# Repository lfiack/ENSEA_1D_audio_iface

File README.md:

# ENSEA_1D_audio_iface
Interface audio (carte son) pour les TP de systèmes numériques en 1D à l'ENSEA

## Make the project work
This project uses a submodule for the KiCAD library. To get it properly, use the `--recursive` option when cloning the repo :
```
git clone --recursive git@github.com:lfiack/ENSEA_1D_audio_iface.git
```

If you forgot the `--recursive` option (as I do quite often), you can type the following command :
```
git submodule update --init --recursive
```

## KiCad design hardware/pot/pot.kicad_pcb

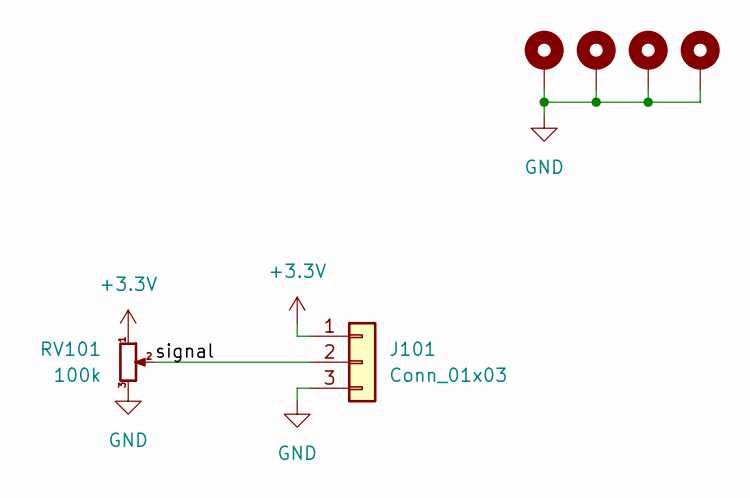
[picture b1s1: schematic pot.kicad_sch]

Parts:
H101, H102, H103, H104: MountingHole_Pad; MountingHole_3.2mm_M3_Pad
J101: Conn_01x03; JST_XH_S3B-XH-A-1_1x03_P2.50mm_Horizontal
RV101: 100k; Potentiometer_Alpha_RD901F-40-00D_Single_Vertical

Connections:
+3.3V: J101.1, RV101.1
/signal: J101.2, RV101.2
GND: H101.1, H102.1, H103.1, H104.1, J101.3, RV101.3

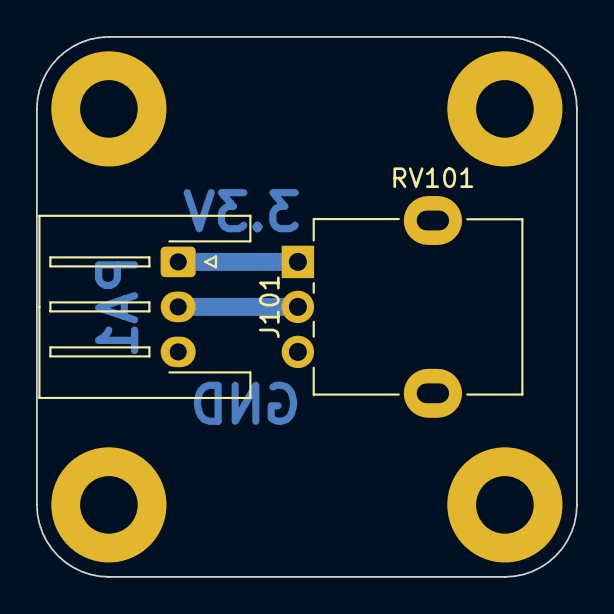
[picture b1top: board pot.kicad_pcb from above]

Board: 2 copper layers, 30.0 x 30.0 mm, 6 parts (0 on the bottom side), 3 nets.

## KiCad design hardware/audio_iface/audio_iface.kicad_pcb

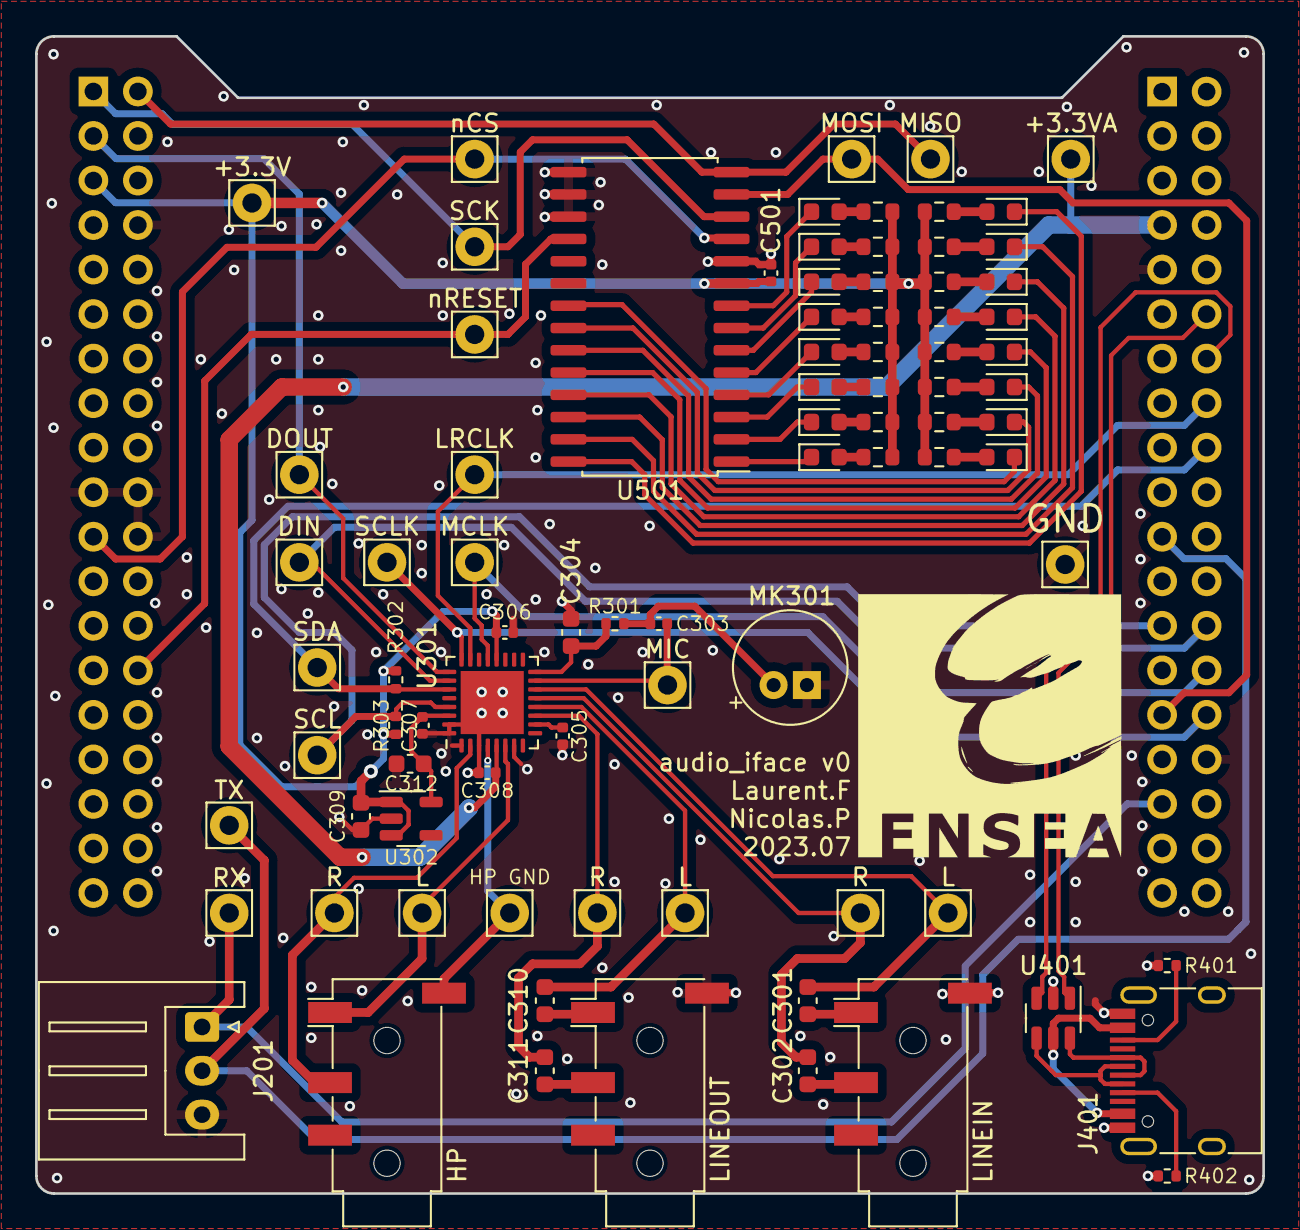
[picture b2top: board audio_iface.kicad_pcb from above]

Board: 2 copper layers, 70.0 x 66.0 mm, 86 parts (0 on the bottom side), 72 nets.

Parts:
C301, C302, C304, C310, C311: 1uF; C_0603_1608Metric
C303, C305, C306, C307, C308, C501: 100nF; C_0402_1005Metric
C309, C312: 1u; C_0603_1608Metric
D501, D502, D503, D504, D505, D509, D510, D511, D512, D513: GREEN; LED_0603_1608Metric
D506, D507, D514, D515: ORANGE; LED_0603_1608Metric
D508, D516: RED; LED_0603_1608Metric
J201: UART; JST_XH_S3B-XH-A_1x03_P2.50mm_Horizontal
J301: LINEIN; Jack_3.5mm_PJ320D_Horizontal
J302: LINEOUT; Jack_3.5mm_PJ320D_Horizontal
J303: HP; Jack_3.5mm_PJ320D_Horizontal
J401: USB_C_Receptacle_USB2.0; USB_C_Receptacle_HRO_TYPE-C-31-M-12
MK301: Microphone; Electret_ABM-713-RC
R301, R401, R402: 5.1k; R_0402_1005Metric
R302, R303: 1.5k; R_0402_1005Metric
R501, R502, R503, R504, R505, R506, R507, R508, R509, R510, R511, R512, R513, R514, R515, R516: R_Small; R_0603_1608Metric
TP101: nRESET; Pin_D1.1mm_L8.5mm_W2.5mm_FlatFork
TP102: MISO; Pin_D1.1mm_L8.5mm_W2.5mm_FlatFork
TP103: MOSI; Pin_D1.1mm_L8.5mm_W2.5mm_FlatFork
TP104: SCK; Pin_D1.1mm_L8.5mm_W2.5mm_FlatFork
TP105: nCS; Pin_D1.1mm_L8.5mm_W2.5mm_FlatFork
TP106: MCLK; Pin_D1.1mm_L8.5mm_W2.5mm_FlatFork
TP107: SCLK; Pin_D1.1mm_L8.5mm_W2.5mm_FlatFork
TP108: LRCLK; Pin_D1.1mm_L8.5mm_W2.5mm_FlatFork
TP109: DIN; Pin_D1.1mm_L8.5mm_W2.5mm_FlatFork
TP110: DOUT; Pin_D1.1mm_L8.5mm_W2.5mm_FlatFork
TP111: SCL; Pin_D1.1mm_L8.5mm_W2.5mm_FlatFork
TP112: SDA; Pin_D1.1mm_L8.5mm_W2.5mm_FlatFork
TP201: +3.3V; Pin_D1.1mm_L8.5mm_W2.5mm_FlatFork
TP202: +3.3VA; Pin_D1.1mm_L8.5mm_W2.5mm_FlatFork
TP203: RX; Pin_D1.1mm_L8.5mm_W2.5mm_FlatFork
TP204: TX; Pin_D1.1mm_L8.5mm_W2.5mm_FlatFork
TP205: GND; Pin_D1.1mm_L8.5mm_W2.5mm_FlatFork
TP301: MIC; Pin_D1.1mm_L8.5mm_W2.5mm_FlatFork
TP302, TP304, TP306: R; Pin_D1.1mm_L8.5mm_W2.5mm_FlatFork
TP303, TP305, TP308: L; Pin_D1.1mm_L8.5mm_W2.5mm_FlatFork
TP307: HP GND; Pin_D1.1mm_L8.5mm_W2.5mm_FlatFork
U201: NUCLEO_L476RG; ST_NUCLEO_64
U301: SGTL5000XNAA3; QFN-32-1EP_5x5mm_P0.5mm_EP3.6x3.6mm
U302: BU18SD2MG-MTR; SOT-23-5
U401: USBLC6-2SC6; SOT-23-6
U501: MCP23S17-E/SO; SOIC-28W_7.5x17.9mm_P1.27mm

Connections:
+1V8: C307.1, C312.1, U301.30 (VDDD), U302.5 (OUT)
+3.3V: C306.1, C309.1, C501.1, R302.1, R303.1, R501.2, R502.2, R503.2, R504.2, R505.2, R506.2, R507.2, R508.2, R509.2, R510.2, R511.2, R512.2, R513.2, R514.2, R515.2, R516.2, TP201.1, U201.105 (VDD), U301.20 (VDDIO), U302.1 (IN), U302.3 (STBY), U501.9 (VDD)
+3.3VA: C308.1, TP202.1, U201.207 (AVDD), U301.5 (VDDA)
/AUDIO CODEC/HP_L: J303.T, TP308.1, U301.6 (HP_L)
/AUDIO CODEC/HP_R: J303.R1, TP306.1, U301.2 (HP_R)
/AUDIO CODEC/HP_VGND: J303.S, TP307.1, U301.4 (HP_VGND)
/AUDIO CODEC/I2C_SCL: R303.2, TP111.1, U201.225 (PB10), U301.29 (CTRL_CLK)
/AUDIO CODEC/I2C_SDA: R302.2, TP112.1, U201.218 (PB11), U301.27 (CTRL_DATA)
/AUDIO CODEC/I2S_DIN: TP109.1, U201.226 (PB15), U301.26 (I2S_DIN)
/AUDIO CODEC/I2S_DOUT: TP110.1, U201.103 (PC12), U301.25 (I2S_DOUT)
/AUDIO CODEC/I2S_LRCLK: TP108.1, U201.216 (PB12), U301.23 (I2S_LRCLK)
/AUDIO CODEC/I2S_SCLK: TP107.1, U201.230 (PB13), U301.24 (I2S_SCLK)
/AUDIO CODEC/LINEIN_L: C301.2, TP303.1, U301.14 (LINEIN_L)
/AUDIO CODEC/LINEIN_R: C302.2, TP302.1, U301.13 (LINEIN_R)
/AUDIO CODEC/LINEOUT_L: C310.1, TP305.1, U301.12 (LINEOUT_L)
/AUDIO CODEC/LINEOUT_R: C311.1, TP304.1, U301.11 (LINEOUT_R)
/AUDIO CODEC/MIC: C303.2, TP301.1, U301.15 (MIC)
/AUDIO CODEC/MIC_BIAS: C304.2, R301.2, U301.16 (MIC_BIAS)
/AUDIO CODEC/SYS_MCLK: TP106.1, U201.228 (PB14), U301.21 (SYS_MCLK)
/AUDIO CODEC/VAG: C305.1, U301.10 (VAG)
/NUCLEO/UART_RX: J201.1, TP203.1, U201.233 (PA10)
/NUCLEO/UART_TX: J201.2, TP204.1, U201.221 (PA9)
/NUCLEO/USB_D+: U201.212 (PA12), U401.1 (I/O1)
/NUCLEO/USB_D-: U201.214 (PA11), U401.3 (I/O2)
/NUCLEO/VU_MISO: TP102.1, U201.102 (PC11), U501.14 (SO)
/NUCLEO/VU_MOSI: TP103.1, U201.229 (PB5), U501.13 (SI)
/NUCLEO/VU_SCK: TP104.1, U201.101 (PC10), U501.12 (SCK)
/NUCLEO/VU_nCS: TP105.1, U201.121 (PB7), U501.11 (~CS)
/NUCLEO/VU_nRESET: TP101.1, U201.128 (PA0), U501.18 (~RESET)
/USB/CC1: J401.A5 (CC1), R402.1
/USB/CC2: J401.B5 (CC2), R401.1
/USB/D+: J401.A6 (D+), J401.B6 (D+), U401.6 (I/O1)
/USB/D-: J401.A7 (D-), J401.B7 (D-), U401.4 (I/O2)
/USB/USBC_VBUS: J401.A4 (VBUS), J401.A9 (VBUS), J401.B4 (VBUS), J401.B9 (VBUS), U401.5 (VBUS)
/VU METER/GPA0: D509.1 (K), U501.21 (GPA0)
/VU METER/GPA1: D510.1 (K), U501.22 (GPA1)
/VU METER/GPA2: D511.1 (K), U501.23 (GPA2)
/VU METER/GPA3: D512.1 (K), U501.24 (GPA3)
/VU METER/GPA4: D513.1 (K), U501.25 (GPA4)
/VU METER/GPA5: D514.1 (K), U501.26 (GPA5)
/VU METER/GPA6: D515.1 (K), U501.27 (GPA6)
/VU METER/GPA7: D516.1 (K), U501.28 (GPA7)
/VU METER/GPB0: D501.1 (K), U501.1 (GPB0)
/VU METER/GPB1: D502.1 (K), U501.2 (GPB1)
/VU METER/GPB2: D503.1 (K), U501.3 (GPB2)
/VU METER/GPB3: D504.1 (K), U501.4 (GPB3)
/VU METER/GPB4: D505.1 (K), U501.5 (GPB4)
/VU METER/GPB5: D506.1 (K), U501.6 (GPB5)
/VU METER/GPB6: D507.1 (K), U501.7 (GPB6)
/VU METER/GPB7: D508.1 (K), U501.8 (GPB7)
GND: C304.1, C305.2, C306.2, C307.2, C308.2, C309.2, C312.2, C501.2, J201.3, J301.S, J302.S, J401.A1 (GND), J401.A12 (GND), J401.B1 (GND), J401.B12 (GND), MK301.1 (-), R401.2, R402.2, TP205.1, U201.108 (GND), U201.119 (GND), U201.120 (GND), U201.122 (GND), U201.209 (GND), U201.220 (GND), U201.232 (AGND), U301.1 (GND), U301.3 (GND), U301.7 (AGND), U301.31 (CTRL_ADR0_CS), U301.32 (CTRL_MODE), U301.33 (GND), U302.2 (GND), U401.2 (GND), U501.10 (VSS), U501.15 (A0), U501.16 (A1), U501.17 (A2)
unnamed: C301.1, J301.T
unnamed: C302.1, J301.R1
unnamed: C310.2, J302.T
unnamed: C311.2, J302.R1
unnamed: D501.2 (A), R501.1
unnamed: D502.2 (A), R502.1
unnamed: D503.2 (A), R503.1
unnamed: D504.2 (A), R504.1
unnamed: D505.2 (A), R505.1
unnamed: D506.2 (A), R506.1
unnamed: D507.2 (A), R507.1
unnamed: D508.2 (A), R508.1
unnamed: D509.2 (A), R509.1
unnamed: D510.2 (A), R510.1
unnamed: D511.2 (A), R511.1
unnamed: D512.2 (A), R512.1
unnamed: D513.2 (A), R513.1
unnamed: D514.2 (A), R514.1
unnamed: D515.2 (A), R515.1
unnamed: D516.2 (A), R516.1
unnamed: C303.1, MK301.2 (+), R301.1

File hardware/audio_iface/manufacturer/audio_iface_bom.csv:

Designator,Comment,Footprint,LCSC Part #
"R301, R401, R402",5.1k,Resistor_SMD:R_0402_1005Metric,C2906948
"D506, D507, D514, D515",ORANGE,LED_SMD:LED_0603_1608Metric,C965801
U301,SGTL5000XNAA3,Package_DFN_QFN:QFN-32-1EP_5x5mm_P0.5mm_EP3.6x3.6mm,C511764
J303,HP,Connector_Audio:Jack_3.5mm_PJ320D_Horizontal,C431535
J302,LINEOUT,Connector_Audio:Jack_3.5mm_PJ320D_Horizontal,C431535
J301,LINEIN,Connector_Audio:Jack_3.5mm_PJ320D_Horizontal,C431535
J401,USB_C_Receptacle_USB2.0,Connector_USB:USB_C_Receptacle_HRO_TYPE-C-31-M-12,C165948
U501,MCP23S17-E/SO,Package_SO:SOIC-28W_7.5x17.9mm_P1.27mm,C145413
"D501, D502, D503, D504, D505, D509, D510, D511, D512, D513",GREEN,LED_SMD:LED_0603_1608Metric,C72043
"C301, C302, C304, C309, C310, C311, C312",1uF,Capacitor_SMD:C_0603_1608Metric,C15849
U401,USBLC6-2SC6,Package_TO_SOT_SMD:SOT-23-6,C7519
"D508, D516",RED,LED_SMD:LED_0603_1608Metric,C2286
"C303, C305, C306, C307, C308, C501",100nF,Capacitor_SMD:C_0402_1005Metric,C1525
U201,NUCLEO_L476RG,WITNS:ST_NUCLEO_64,
TP307,HP GND,Connector_Pin:Pin_D1.1mm_L8.5mm_W2.5mm_FlatFork,
"TP303, TP305, TP308",L,Connector_Pin:Pin_D1.1mm_L8.5mm_W2.5mm_FlatFork,
"TP302, TP304, TP306",R,Connector_Pin:Pin_D1.1mm_L8.5mm_W2.5mm_FlatFork,
TP301,MIC,Connector_Pin:Pin_D1.1mm_L8.5mm_W2.5mm_FlatFork,
TP205,GND,Connector_Pin:Pin_D1.1mm_L8.5mm_W2.5mm_FlatFork,
TP204,TX,Connector_Pin:Pin_D1.1mm_L8.5mm_W2.5mm_FlatFork,
TP203,RX,Connector_Pin:Pin_D1.1mm_L8.5mm_W2.5mm_FlatFork,
TP202,+3.3VA,Connector_Pin:Pin_D1.1mm_L8.5mm_W2.5mm_FlatFork,
TP201,+3.3V,Connector_Pin:Pin_D1.1mm_L8.5mm_W2.5mm_FlatFork,
TP112,SDA,Connector_Pin:Pin_D1.1mm_L8.5mm_W2.5mm_FlatFork,
TP111,SCL,Connector_Pin:Pin_D1.1mm_L8.5mm_W2.5mm_FlatFork,
TP110,DOUT,Connector_Pin:Pin_D1.1mm_L8.5mm_W2.5mm_FlatFork,
TP109,DIN,Connector_Pin:Pin_D1.1mm_L8.5mm_W2.5mm_FlatFork,
TP108,LRCLK,Connector_Pin:Pin_D1.1mm_L8.5mm_W2.5mm_FlatFork,
TP107,SCLK,Connector_Pin:Pin_D1.1mm_L8.5mm_W2.5mm_FlatFork,
TP106,MCLK,Connector_Pin:Pin_D1.1mm_L8.5mm_W2.5mm_FlatFork,
TP105,nCS,Connector_Pin:Pin_D1.1mm_L8.5mm_W2.5mm_FlatFork,
TP104,SCK,Connector_Pin:Pin_D1.1mm_L8.5mm_W2.5mm_FlatFork,
TP103,MOSI,Connector_Pin:Pin_D1.1mm_L8.5mm_W2.5mm_FlatFork,
TP102,MISO,Connector_Pin:Pin_D1.1mm_L8.5mm_W2.5mm_FlatFork,
TP101,nRESET,Connector_Pin:Pin_D1.1mm_L8.5mm_W2.5mm_FlatFork,
"R506, R507, R508, R514, R515, R516",680,Resistor_SMD:R_0603_1608Metric,
"R501, R502, R503, R504, R505, R509, R510, R511, R512, R513",560,Resistor_SMD:R_0603_1608Metric,
"R302, R303",1.5k,Resistor_SMD:R_0402_1005Metric,
MK301,Microphone,WITNS:Electret_ABM-713-RC,
J201,UART,Connector_JST:JST_XH_S3B-XH-A_1x03_P2.50mm_Horizontal,

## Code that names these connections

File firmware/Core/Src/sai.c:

/* USER CODE BEGIN Header */
/**
  ******************************************************************************
  * File Name          : SAI.c
  * Description        : This file provides code for the configuration
  *                      of the SAI instances.
  ******************************************************************************
  * @attention
  *
  * Copyright (c) 2023 STMicroelectronics.
  * All rights reserved.
  *
  * This software is licensed under terms that can be found in the LICENSE file
  * in the root directory of this software component.
  * If no LICENSE file comes with this software, it is provided AS-IS.
  *
  ******************************************************************************
  */
/* USER CODE END Header */

/* Includes ------------------------------------------------------------------*/
#include "sai.h"

/* USER CODE BEGIN 0 */

/* USER CODE END 0 */

SAI_HandleTypeDef hsai_BlockA2;
SAI_HandleTypeDef hsai_BlockB2;
DMA_HandleTypeDef hdma_sai2_a;
DMA_HandleTypeDef hdma_sai2_b;

/* SAI2 init function */
void MX_SAI2_Init(void)
{

  /* USER CODE BEGIN SAI2_Init 0 */

  /* USER CODE END SAI2_Init 0 */

  /* USER CODE BEGIN SAI2_Init 1 */

  /* USER CODE END SAI2_Init 1 */

  /* USER CODE BEGIN SAI2_Init 1 */

  /* USER CODE END SAI2_Init 1 */

  hsai_BlockA2.Instance = SAI2_Block_A;
  hsai_BlockA2.Init.AudioMode = SAI_MODEMASTER_TX;
  hsai_BlockA2.Init.Synchro = SAI_ASYNCHRONOUS;
  hsai_BlockA2.Init.OutputDrive = SAI_OUTPUTDRIVE_DISABLE;
  hsai_BlockA2.Init.NoDivider = SAI_MASTERDIVIDER_ENABLE;
  hsai_BlockA2.Init.FIFOThreshold = SAI_FIFOTHRESHOLD_EMPTY;
  hsai_BlockA2.Init.AudioFrequency = SAI_AUDIO_FREQUENCY_48K;
  hsai_BlockA2.Init.SynchroExt = SAI_SYNCEXT_DISABLE;
  hsai_BlockA2.Init.MonoStereoMode = SAI_STEREOMODE;
  hsai_BlockA2.Init.CompandingMode = SAI_NOCOMPANDING;
  hsai_BlockA2.Init.TriState = SAI_OUTPUT_NOTRELEASED;
  if (HAL_SAI_InitProtocol(&hsai_BlockA2, SAI_I2S_STANDARD, SAI_PROTOCOL_DATASIZE_16BIT, 2) != HAL_OK)
  {
    Error_Handler();
  }
  hsai_BlockB2.Instance = SAI2_Block_B;
  hsai_BlockB2.Init.AudioMode = SAI_MODESLAVE_RX;
  hsai_BlockB2.Init.Synchro = SAI_SYNCHRONOUS;
  hsai_BlockB2.Init.OutputDrive = SAI_OUTPUTDRIVE_DISABLE;
  hsai_BlockB2.Init.FIFOThreshold = SAI_FIFOTHRESHOLD_EMPTY;
  hsai_BlockB2.Init.SynchroExt = SAI_SYNCEXT_DISABLE;
  hsai_BlockB2.Init.MonoStereoMode = SAI_STEREOMODE;
  hsai_BlockB2.Init.CompandingMode = SAI_NOCOMPANDING;
  hsai_BlockB2.Init.TriState = SAI_OUTPUT_NOTRELEASED;
  if (HAL_SAI_InitProtocol(&hsai_BlockB2, SAI_I2S_STANDARD, SAI_PROTOCOL_DATASIZE_16BIT, 2) != HAL_OK)
  {
    Error_Handler();
  }
  /* USER CODE BEGIN SAI2_Init 2 */

  /* USER CODE END SAI2_Init 2 */

}
static uint32_t SAI2_client =0;

void HAL_SAI_MspInit(SAI_HandleTypeDef* saiHandle)
{

  GPIO_InitTypeDef GPIO_InitStruct;
/* SAI2 */
    if(saiHandle->Instance==SAI2_Block_A)
    {
    /* SAI2 clock enable */
    if (SAI2_client == 0)
    {
       __HAL_RCC_SAI2_CLK_ENABLE();

    /* Peripheral interrupt init*/
    HAL_NVIC_SetPriority(SAI2_IRQn, 0, 0);
    HAL_NVIC_EnableIRQ(SAI2_IRQn);
    }
    SAI2_client ++;

    /**SAI2_A_Block_A GPIO Configuration
    PB12     ------> SAI2_FS_A
    PB13     ------> SAI2_SCK_A
    PB14     ------> SAI2_MCLK_A
    PB15     ------> SAI2_SD_A
    */
    GPIO_InitStruct.Pin = GPIO_PIN_12|GPIO_PIN_13|GPIO_PIN_14|GPIO_PIN_15;
    GPIO_InitStruct.Mode = GPIO_MODE_AF_PP;
    GPIO_InitStruct.Pull = GPIO_NOPULL;
    GPIO_InitStruct.Speed = GPIO_SPEED_FREQ_LOW;
    GPIO_InitStruct.Alternate = GPIO_AF13_SAI2;
    HAL_GPIO_Init(GPIOB, &GPIO_InitStruct);

    /* Peripheral DMA init*/

    hdma_sai2_a.Instance = DMA1_Channel6;
    hdma_sai2_a.Init.Request = DMA_REQUEST_1;
    hdma_sai2_a.Init.Direction = DMA_MEMORY_TO_PERIPH;
    hdma_sai2_a.Init.PeriphInc = DMA_PINC_DISABLE;
    hdma_sai2_a.Init.MemInc = DMA_MINC_ENABLE;
    hdma_sai2_a.Init.PeriphDataAlignment = DMA_PDATAALIGN_HALFWORD;
    hdma_sai2_a.Init.MemDataAlignment = DMA_MDATAALIGN_HALFWORD;
    hdma_sai2_a.Init.Mode = DMA_CIRCULAR;
    hdma_sai2_a.Init.Priority = DMA_PRIORITY_LOW;
    if (HAL_DMA_Init(&hdma_sai2_a) != HAL_OK)
    {
      Error_Handler();
    }

    /* Several peripheral DMA handle pointers point to the same DMA handle.
     Be aware that there is only one channel to perform all the requested DMAs. */
    __HAL_LINKDMA(saiHandle,hdmarx,hdma_sai2_a);
    __HAL_LINKDMA(saiHandle,hdmatx,hdma_sai2_a);
    }
    if(saiHandle->Instance==SAI2_Block_B)
    {
      /* SAI2 clock enable */
      if (SAI2_client == 0)
      {
       __HAL_RCC_SAI2_CLK_ENABLE();

      /* Peripheral interrupt init*/
      HAL_NVIC_SetPriority(SAI2_IRQn, 0, 0);
      HAL_NVIC_EnableIRQ(SAI2_IRQn);
      }
    SAI2_client ++;

    /**SAI2_B_Block_B GPIO Configuration
    PC12     ------> SAI2_SD_B
    */
    GPIO_InitStruct.Pin = GPIO_PIN_12;
    GPIO_InitStruct.Mode = GPIO_MODE_AF_PP;
    GPIO_InitStruct.Pull = GPIO_NOPULL;
    GPIO_InitStruct.Speed = GPIO_SPEED_FREQ_LOW;
    GPIO_InitStruct.Alternate = GPIO_AF13_SAI2;
    HAL_GPIO_Init(GPIOC, &GPIO_InitStruct);

    /* Peripheral DMA init*/

    hdma_sai2_b.Instance = DMA1_Channel7;
    hdma_sai2_b.Init.Request = DMA_REQUEST_1;
    hdma_sai2_b.Init.Direction = DMA_PERIPH_TO_MEMORY;
    hdma_sai2_b.Init.PeriphInc = DMA_PINC_DISABLE;
    hdma_sai2_b.Init.MemInc = DMA_MINC_ENABLE;
    hdma_sai2_b.Init.PeriphDataAlignment = DMA_PDATAALIGN_HALFWORD;
    hdma_sai2_b.Init.MemDataAlignment = DMA_MDATAALIGN_HALFWORD;
    hdma_sai2_b.Init.Mode = DMA_CIRCULAR;
    hdma_sai2_b.Init.Priority = DMA_PRIORITY_LOW;
    if (HAL_DMA_Init(&hdma_sai2_b) != HAL_OK)
    {
      Error_Handler();
    }

    /* Several peripheral DMA handle pointers point to the same DMA handle.
     Be aware that there is only one channel to perform all the requested DMAs. */
    __HAL_LINKDMA(saiHandle,hdmarx,hdma_sai2_b);
    __HAL_LINKDMA(saiHandle,hdmatx,hdma_sai2_b);
    }
}

void HAL_SAI_MspDeInit(SAI_HandleTypeDef* saiHandle)
{

/* SAI2 */
    if(saiHandle->Instance==SAI2_Block_A)
    {
    SAI2_client --;
    if (SAI2_client == 0)
      {
      /* Peripheral clock disable */
       __HAL_RCC_SAI2_CLK_DISABLE();
      HAL_NVIC_DisableIRQ(SAI2_IRQn);
      }

    /**SAI2_A_Block_A GPIO Configuration
    PB12     ------> SAI2_FS_A
    PB13     ------> SAI2_SCK_A
    PB14     ------> SAI2_MCLK_A
    PB15     ------> SAI2_SD_A
    */
    HAL_GPIO_DeInit(GPIOB, GPIO_PIN_12|GPIO_PIN_13|GPIO_PIN_14|GPIO_PIN_15);

    HAL_DMA_DeInit(saiHandle->hdmarx);
    HAL_DMA_DeInit(saiHandle->hdmatx);
    }
    if(saiHandle->Instance==SAI2_Block_B)
    {
    SAI2_client --;
      if (SAI2_client == 0)
      {
      /* Peripheral clock disable */
      __HAL_RCC_SAI2_CLK_DISABLE();
      HAL_NVIC_DisableIRQ(SAI2_IRQn);
      }

    /**SAI2_B_Block_B GPIO Configuration
    PC12     ------> SAI2_SD_B
    */
    HAL_GPIO_DeInit(GPIOC, GPIO_PIN_12);

    HAL_DMA_DeInit(saiHandle->hdmarx);
    HAL_DMA_DeInit(saiHandle->hdmatx);
    }
}

/**
  * @}
  */

/**
  * @}
  */

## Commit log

2023-06-20 symbol & footprint
2023-06-20 added some connections
2023-06-27 Added LEDs
2023-06-28 schematic v1 done
2023-06-30 crude placement
2023-07-03 routing v1
2023-07-17 logo ensea
2023-07-17 add logo
2023-09-18 First firmware, playing with LEDs
2023-10-02 I2C of SGTL5000 working
2023-10-05 tests SAI/SGTL
2023-11-22 test SAI I2S
2023-11-23 code CODEC
2023-11-24 registers for SGTL5000
2023-11-27 THE DAC WORKS!!
2023-11-28 code for ADC not tested
2023-11-30 SGTL working both ways
2024-01-22 carte potards
